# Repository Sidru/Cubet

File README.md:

# Cubet (CUBID-19) 

Cubet, a small single color led cube, build during the Covid-19 Quarantine

:warning: The README is still in working process

:warning: The Software works, but it must be improved. Trying to get the DMA to work with the Timer Counter to automatic set the LATCH output. The animations must be still coded (I've copied some animations and functions from [fuchsales/LED-Cube](https://github.com/fuchsalex/LED-Cube)

I always wanted a LED Cube, a compact one with smd leds. I also wanted to give KiCad a try (I've been Eagle user for a couple of years). That's why I started this mini project.

My goal was: 
- Small LED Cube, not bigger than 5cm
- No extra power needed (USB powered)
- Cheap (i.e. Shift Register instead of "expensive" LED Drivers, no SK6812/ws2811 leds)
- Designed with KiCad

I started with the Schematic and Layout in January, and the PCB came together with COVID, so I had plenty of time to solder.
I gave my cube the name of Cubet (catalan word for small cube), but CUBID is also a good name :)

The microcontroller is a SAMD21, with native USB, so no FTDI or similar is needed. It' a simple Arduino Zero compatible board, like the Feather M0 from Adafruit
It uses 74HC595 Shift Registers and a couple of transistors.

My tools are not the best one, and I realized I may need to buy better and new tools. For example my soldering iron is a cheap one and the soldering was quite a challenge (The head was too big for some components, and it didn't get hot enough). 
I also may need a Microscope, it's more pleasant than a magnifying glass. The tweezers were of course also too big. 

For the LED Matrix/Cube I need to develope a helping tool or something similar. My idea was to use 8 big holes in the PCB to put there 8 LEDS and solder them together to get a column. This didn't work as expected so I neede to solder without help.
I used 0.3mm Wire for the columns, and 0.2mm Wire for the rest.

## Getting Started

* Install KiCad and make changes to the schematic/layout (if needed)
* Get the PCB from your favourite Producer
* Solder all the components
* Flash the Bootloader (if needed)
* Flash the Software

#### Prerequisites

* A lot of time 
* Patience
* More patience
* Soldering skill
* JTAG Programmer (I used an J\-LINK EDU Mini)
* More time
* Did I mention patience?

### Installing 
#### Flashing the Bootloader
#### Flashing the Software

## Built With

* [KiCad](http://www.kicad-pcb.org)
* [PlatformIO](http://platformio.org)

## Authors

## License

This project is licensed under the Apache License - see the [LICENSE.md](LICENSE.md) file for tedtails

## Acknowledgments

[LED-Cube](https://github.com/fuchsalex/LED-Cube)
[Mini KiCad Tutorial](https://github.com/MalphasWats/hawk)
[KiCad Freerouting](https://github.com/miho/freerouting)
[Gerber Export](https://jnduli.co.ke/prepare-kicad-pcb-elecrow.html)
[PCB from Elecrow](https://www.elecrow.com/pcb-manufacturing.html)
[SAMD21](http://ww1.microchip.com/downloads/en/DeviceDoc/SAM_D21_DA1_Family_DataSheet_DS40001882F.pdf)
[SAMD21 GDB](https://learn.adafruit.com/debugging-the-samd21-with-gdb/setup)
[SAMD21 Bootloader Protection](https://roamingthings.de/posts/use-j-link-to-change-the-boot-loader-protection-of-a-sam-d21)
[Programming a SAMD bootloader using JLink & Linux](https://hackaday.io/page/5997-programming-a-samd-bootloader-using-jlink-linux)
[SAMD21\_DMA](https://aykevl.nl/2019/09/samd21-dma)
[Adafruit\_ZeroDMA](https://github.com/adafruit/Adafruit\_ZeroDMA)

## Future changes

* RGB leds 
* ESP32 for Blueetoth and WLAN
* SPI, I2C and UART connectors for hardware "upgrades"
* Battery connector and battery charging
* Maybe a 12x12x12 and a 16x16x16 version
* SD card for animations without programming

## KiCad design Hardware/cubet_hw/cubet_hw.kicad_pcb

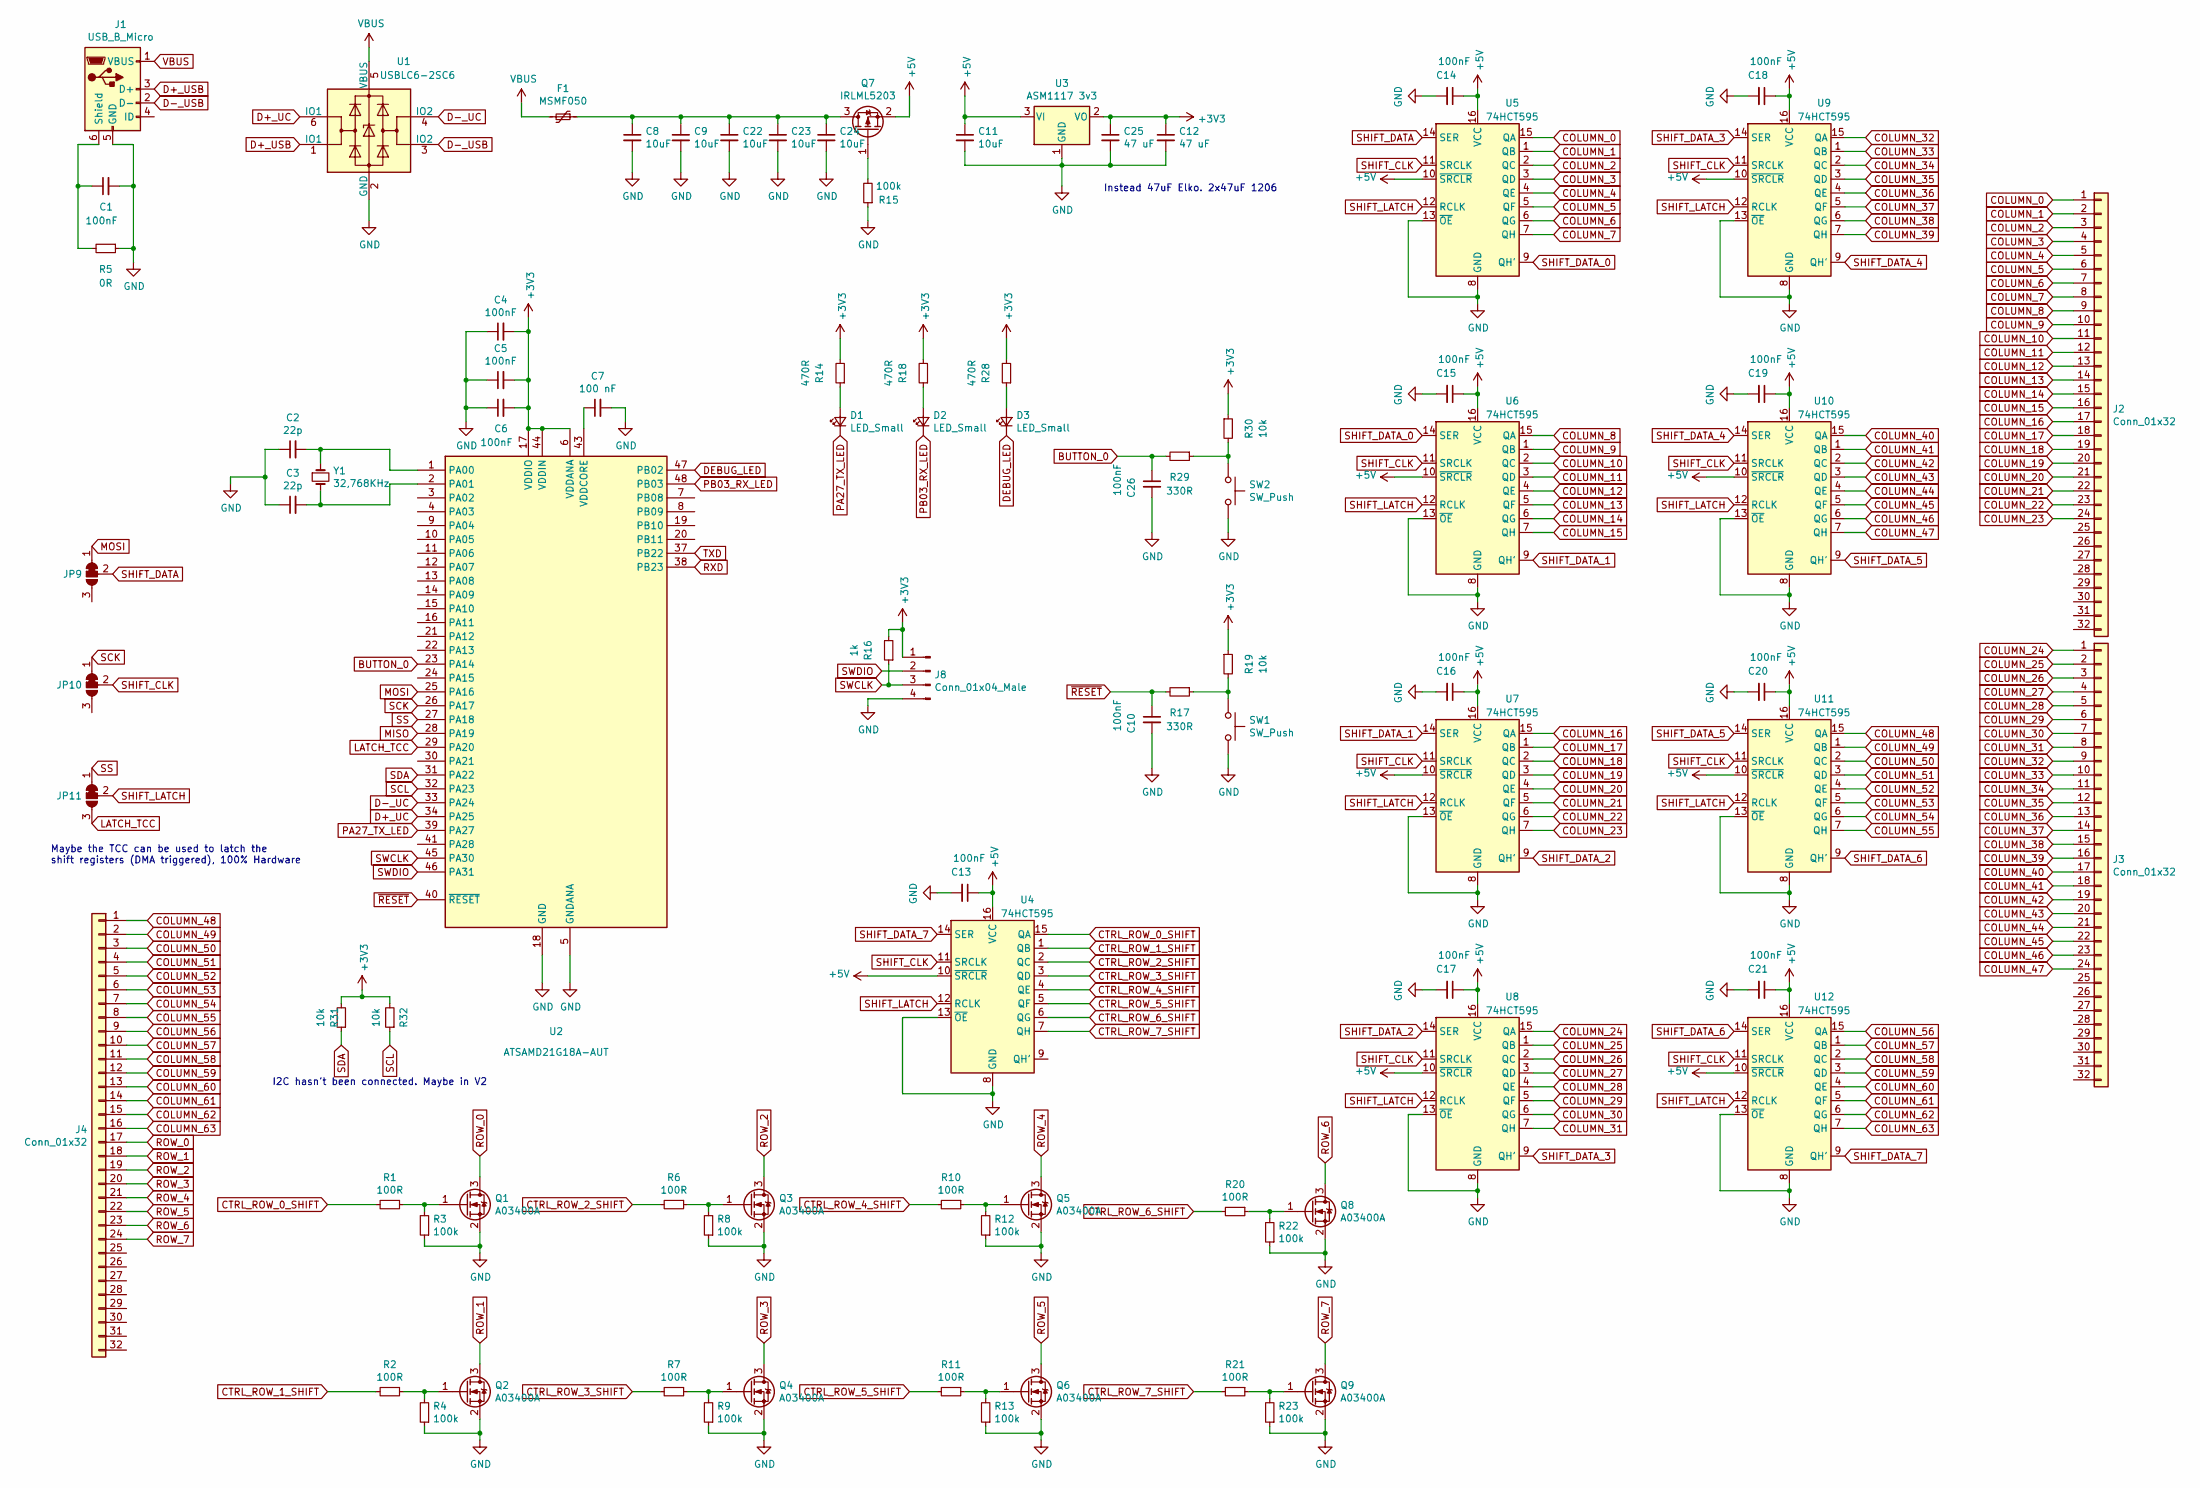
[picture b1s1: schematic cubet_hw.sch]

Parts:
C1, C4, C5, C6, C10, C13, C14, C15, C16, C17, C18, C19, C20, C21, C26: 100nF; C_0603_1608Metric
C2, C3: 22p; C_0603_1608Metric
C7: 100 nF; C_0603_1608Metric
C8, C9, C11, C22, C23, C24: 10uF; C_1206_3216Metric_Pad1.42x1.75mm_HandSolder
C12, C25: 47 uF; C_1206_3216Metric_Pad1.42x1.75mm_HandSolder
D1, D2, D3: LED_Small; LED_0603_1608Metric_Pad1.05x0.95mm_HandSolder
F1: MSMF050; Fuse_1812_4532Metric_Pad1.30x3.40mm_HandSolder
J1: USB_B_Micro; USB_Micro-B_Amphenol_10103594-0001LF_Horizontal
J2, J3, J4: Conn_01x32; PinSocket_1x32_P1.27mm_Vertical
J8: Conn_01x04_Male; PinHeader_1x04_P1.27mm_Horizontal
JP9, JP10, JP11: SolderJumper_3_Bridged12; SolderJumper-3_P1.3mm_Bridged12_RoundedPad1.0x1.5mm
Q1, Q2, Q3, Q4, Q5, Q6, Q8, Q9: A03400A; SOT-23
Q7: IRLML5203; SOT-23_Handsoldering
R1, R2, R6, R7, R10, R11, R20, R21: 100R; R_0603_1608Metric_Pad1.05x0.95mm_HandSolder
R3, R4, R8, R9, R12, R13, R22, R23: 100k; R_0603_1608Metric_Pad1.05x0.95mm_HandSolder
R5: 0R; R_0603_1608Metric
R14, R18, R28: 470R; R_0603_1608Metric_Pad1.05x0.95mm_HandSolder
R15: 100k; R_0603_1608Metric
R16: 1k; R_0603_1608Metric
R17, R29: 330R; R_0603_1608Metric
R19, R30: 10k; R_0603_1608Metric
R31, R32: 10k; R_0603_1608Metric_Pad1.05x0.95mm_HandSolder
SW1, SW2: SW_Push; SW_SPST_EVQP7A
U1: USBLC6-2SC6; SOT-23-6
U2: ATSAMD21G18A-AUT; TQFP-48_7x7mm_P0.5mm
U3: ASM1117 3v3; SOT-223
U4, U5, U6, U7, U8, U9, U10, U11, U12: 74HCT595; SOP-16_4.55x10.3mm_P1.27mm
Y1: 32,768KHz; Crystal_SMD_2012-2Pin_2.0x1.2mm_HandSoldering

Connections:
+3V3: C4.2, C5.2, C6.2, C12.1, C25.1, J8.1, R14.2, R16.2, R18.2, R19.1, R28.2, R30.1, R31.2, R32.2, U2.6 (VDDANA), U2.17 (VDDIO), U2.36 (VDDIO), U2.44 (VDDIN), U3.2 (VO)
+5V: C11.1, C13.1, C14.1, C15.1, C16.1, C17.1, C18.1, C19.1, C20.1, C21.1, Q7.2 (S), U3.3 (VI), U4.10 (~SRCLR), U4.16 (VCC), U5.10 (~SRCLR), U5.16 (VCC), U6.10 (~SRCLR), U6.16 (VCC), U7.10 (~SRCLR), U7.16 (VCC), U8.10 (~SRCLR), U8.16 (VCC), U9.10 (~SRCLR), U9.16 (VCC), U10.10 (~SRCLR), U10.16 (VCC), U11.10 (~SRCLR), U11.16 (VCC), U12.10 (~SRCLR), U12.16 (VCC)
BUTTON_0: C26.1, R29.2, U2.23 (PA14)
COLUMN_0: J2.1, U5.15 (QA)
COLUMN_1: J2.2, U5.1 (QB)
COLUMN_2: J2.3, U5.2 (QC)
COLUMN_3: J2.4, U5.3 (QD)
COLUMN_4: J2.5, U5.4 (QE)
COLUMN_5: J2.6, U5.5 (QF)
COLUMN_6: J2.7, U5.6 (QG)
COLUMN_7: J2.8, U5.7 (QH)
COLUMN_8: J2.9, U6.15 (QA)
COLUMN_9: J2.10, U6.1 (QB)
COLUMN_10: J2.11, U6.2 (QC)
COLUMN_11: J2.12, U6.3 (QD)
COLUMN_12: J2.13, U6.4 (QE)
COLUMN_13: J2.14, U6.5 (QF)
COLUMN_14: J2.15, U6.6 (QG)
COLUMN_15: J2.16, U6.7 (QH)
COLUMN_16: J2.17, U7.15 (QA)
COLUMN_17: J2.18, U7.1 (QB)
COLUMN_18: J2.19, U7.2 (QC)
COLUMN_19: J2.20, U7.3 (QD)
COLUMN_20: J2.21, U7.4 (QE)
COLUMN_21: J2.22, U7.5 (QF)
COLUMN_22: J2.23, U7.6 (QG)
COLUMN_23: J2.24, U7.7 (QH)
COLUMN_24: J3.1, U8.15 (QA)
COLUMN_25: J3.2, U8.1 (QB)
COLUMN_26: J3.3, U8.2 (QC)
COLUMN_27: J3.4, U8.3 (QD)
COLUMN_28: J3.5, U8.4 (QE)
COLUMN_29: J3.6, U8.5 (QF)
COLUMN_30: J3.7, U8.6 (QG)
COLUMN_31: J3.8, U8.7 (QH)
COLUMN_32: J3.9, U9.15 (QA)
COLUMN_33: J3.10, U9.1 (QB)
COLUMN_34: J3.11, U9.2 (QC)
COLUMN_35: J3.12, U9.3 (QD)
COLUMN_36: J3.13, U9.4 (QE)
COLUMN_37: J3.14, U9.5 (QF)
COLUMN_38: J3.15, U9.6 (QG)
COLUMN_39: J3.16, U9.7 (QH)
COLUMN_40: J3.17, U10.15 (QA)
COLUMN_41: J3.18, U10.1 (QB)
COLUMN_42: J3.19, U10.2 (QC)
COLUMN_43: J3.20, U10.3 (QD)
COLUMN_44: J3.21, U10.4 (QE)
COLUMN_45: J3.22, U10.5 (QF)
COLUMN_46: J3.23, U10.6 (QG)
COLUMN_47: J3.24, U10.7 (QH)
COLUMN_48: J4.1, U11.15 (QA)
COLUMN_49: J4.2, U11.1 (QB)
COLUMN_50: J4.3, U11.2 (QC)
COLUMN_51: J4.4, U11.3 (QD)
COLUMN_52: J4.5, U11.4 (QE)
COLUMN_53: J4.6, U11.5 (QF)
COLUMN_54: J4.7, U11.6 (QG)
COLUMN_55: J4.8, U11.7 (QH)
COLUMN_56: J4.9, U12.15 (QA)
COLUMN_57: J4.10, U12.1 (QB)
COLUMN_58: J4.11, U12.2 (QC)
COLUMN_59: J4.12, U12.3 (QD)
COLUMN_60: J4.13, U12.4 (QE)
COLUMN_61: J4.14, U12.5 (QF)
COLUMN_62: J4.15, U12.6 (QG)
COLUMN_63: J4.16, U12.7 (QH)
CTRL_ROW_0_SHIFT: R1.2, U4.15 (QA)
CTRL_ROW_0_UC: U2.9 (PA04)
CTRL_ROW_1_SHIFT: R2.2, U4.1 (QB)
CTRL_ROW_1_UC: U2.10 (PA05)
CTRL_ROW_2_SHIFT: R6.2, U4.2 (QC)
CTRL_ROW_2_UC: U2.11 (PA06)
CTRL_ROW_3_SHIFT: R7.2, U4.3 (QD)
CTRL_ROW_3_UC: U2.12 (PA07)
CTRL_ROW_4_SHIFT: R10.2, U4.4 (QE)
CTRL_ROW_4_UC: U2.13 (PA08)
CTRL_ROW_5_SHIFT: R11.2, U4.5 (QF)
CTRL_ROW_5_UC: U2.14 (PA09)
CTRL_ROW_6_SHIFT: R20.2, U4.6 (QG)
CTRL_ROW_6_UC: U2.15 (PA10)
CTRL_ROW_7_SHIFT: R21.2, U4.7 (QH)
CTRL_ROW_7_UC: U2.16 (PA11)
D+_UC: U1.6 (IO1), U2.34 (PA25)
D+_USB: J1.3 (D+), U1.1 (IO1)
D-_UC: U1.4 (IO2), U2.33 (PA24)
D-_USB: J1.2 (D-), U1.3 (IO2)
DEBUG_LED: D3.1 (K), U2.47 (PB02)
GND: C1.2, C2.1, C3.1, C4.1, C5.1, C6.1, C7.2, C8.2, C9.2, C10.2, C11.2, C12.2, C13.2, C14.2, C15.2, C16.2, C17.2, C18.2, C19.2, C20.2, C21.2, C22.2, C23.2, C24.2, C25.2, C26.2, J1.5 (GND), J8.4, Q1.2 (S), Q2.2 (S), Q3.2 (S), Q4.2 (S), Q5.2 (S), Q6.2 (S), Q8.2 (S), Q9.2 (S), R3.1, R4.1, R5.1, R8.1, R9.1, R12.1, R13.1, R15.1, R22.1, R23.1, SW1.2, SW2.2, U1.2 (GND), U2.5 (GNDANA), U2.18 (GND), U2.35 (GND), U2.42 (GND), U3.1 (GND), U4.8 (GND), U4.13 (~OE), U5.8 (GND), U5.13 (~OE), U6.8 (GND), U6.13 (~OE), U7.8 (GND), U7.13 (~OE), U8.8 (GND), U8.13 (~OE), U9.8 (GND), U9.13 (~OE), U10.8 (GND), U10.13 (~OE), U11.8 (GND), U11.13 (~OE), U12.8 (GND), U12.13 (~OE)
LATCH_TCC: JP11.3 (B), U2.29 (PA20)
MISO: U2.28 (PA19)
MOSI: JP9.1 (A), U2.25 (PA16)
unnamed: C1.1, J1.6 (Shield), R5.2
unnamed: C2.2, U2.1 (PA00), Y1.1
unnamed: C3.2, U2.2 (PA01), Y1.2
unnamed: C7.1, U2.43 (VDDCORE)
unnamed: C8.1, C9.1, C22.1, C23.1, C24.1, F1.1, Q7.3 (D)
unnamed: D1.2 (A), R14.1
unnamed: D2.2 (A), R18.1
unnamed: D3.2 (A), R28.1
unnamed: Q1.1 (G), R1.1, R3.2
unnamed: Q2.1 (G), R2.1, R4.2
unnamed: Q3.1 (G), R6.1, R8.2
unnamed: Q4.1 (G), R7.1, R9.2
unnamed: Q5.1 (G), R10.1, R12.2
unnamed: Q6.1 (G), R11.1, R13.2
unnamed: Q7.1 (G), R15.2
unnamed: Q8.1 (G), R20.1, R22.2
unnamed: Q9.1 (G), R21.1, R23.2
unnamed: R17.1, R19.2, SW1.1
unnamed: R29.1, R30.2, SW2.1
PA27_TX_LED: D1.1 (K), U2.39 (PA27)
PB03_RX_LED: D2.1 (K), U2.48 (PB03)
PB10_S4_SPI_MOSI: U2.19 (PB10)
PB11_S4_SPI_SCK: U2.20 (PB11)
PB12_S4_SPI_MISO: U2.21 (PA12)
ROW_0: J4.17, Q1.3 (D)
ROW_1: J4.18, Q2.3 (D)
ROW_2: J4.19, Q3.3 (D)
ROW_3: J4.20, Q4.3 (D)
ROW_4: J4.21, Q5.3 (D)
ROW_5: J4.22, Q6.3 (D)
ROW_6: J4.23, Q8.3 (D)
ROW_7: J4.24, Q9.3 (D)
RXD: U2.38 (PB23)
SCK: JP10.1 (A), U2.26 (PA17)
SCL: R32.1, U2.32 (PA23)
SDA: R31.1, U2.31 (PA22)
SHIFT_CLK: JP10.2 (C), U4.11 (SRCLK), U5.11 (SRCLK), U6.11 (SRCLK), U7.11 (SRCLK), U8.11 (SRCLK), U9.11 (SRCLK), U10.11 (SRCLK), U11.11 (SRCLK), U12.11 (SRCLK)
SHIFT_DATA: JP9.2 (C), U5.14 (SER)
SHIFT_DATA_0: U5.9 (QH'), U6.14 (SER)
SHIFT_DATA_1: U6.9 (QH'), U7.14 (SER)
SHIFT_DATA_2: U7.9 (QH'), U8.14 (SER)
SHIFT_DATA_3: U8.9 (QH'), U9.14 (SER)
SHIFT_DATA_4: U9.9 (QH'), U10.14 (SER)
SHIFT_DATA_5: U10.9 (QH'), U11.14 (SER)
SHIFT_DATA_6: U11.9 (QH'), U12.14 (SER)
SHIFT_DATA_7: U4.14 (SER), U12.9 (QH')
SHIFT_LATCH: JP11.2 (C), U4.12 (RCLK), U5.12 (RCLK), U6.12 (RCLK), U7.12 (RCLK), U8.12 (RCLK), U9.12 (RCLK), U10.12 (RCLK), U11.12 (RCLK), U12.12 (RCLK)
SS: JP11.1 (A), U2.27 (PA18)
SWCLK: J8.3, R16.1, U2.45 (PA30)
SWDIO: J8.2, U2.46 (PA31)
TXD: U2.37 (PB22)
VBUS: F1.2, J1.1 (VBUS), U1.5 (VBUS)
~RESET~: C10.1, R17.2, U2.40 (~RESET)

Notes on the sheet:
Instead 47uF Elko. 2x47uF 1206
Maybe the TCC can be used to latch the shift registers (DMA triggered), 100% Hardware
I2C hasn't been connected. Maybe in V2

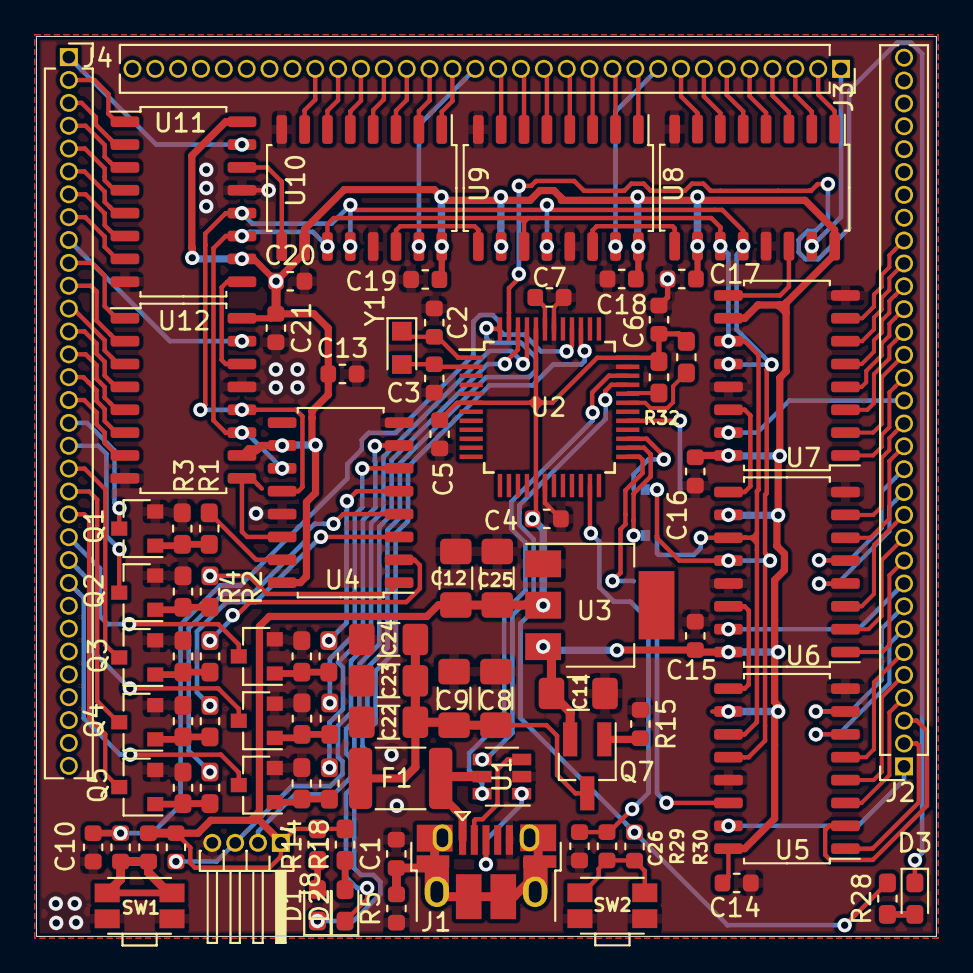
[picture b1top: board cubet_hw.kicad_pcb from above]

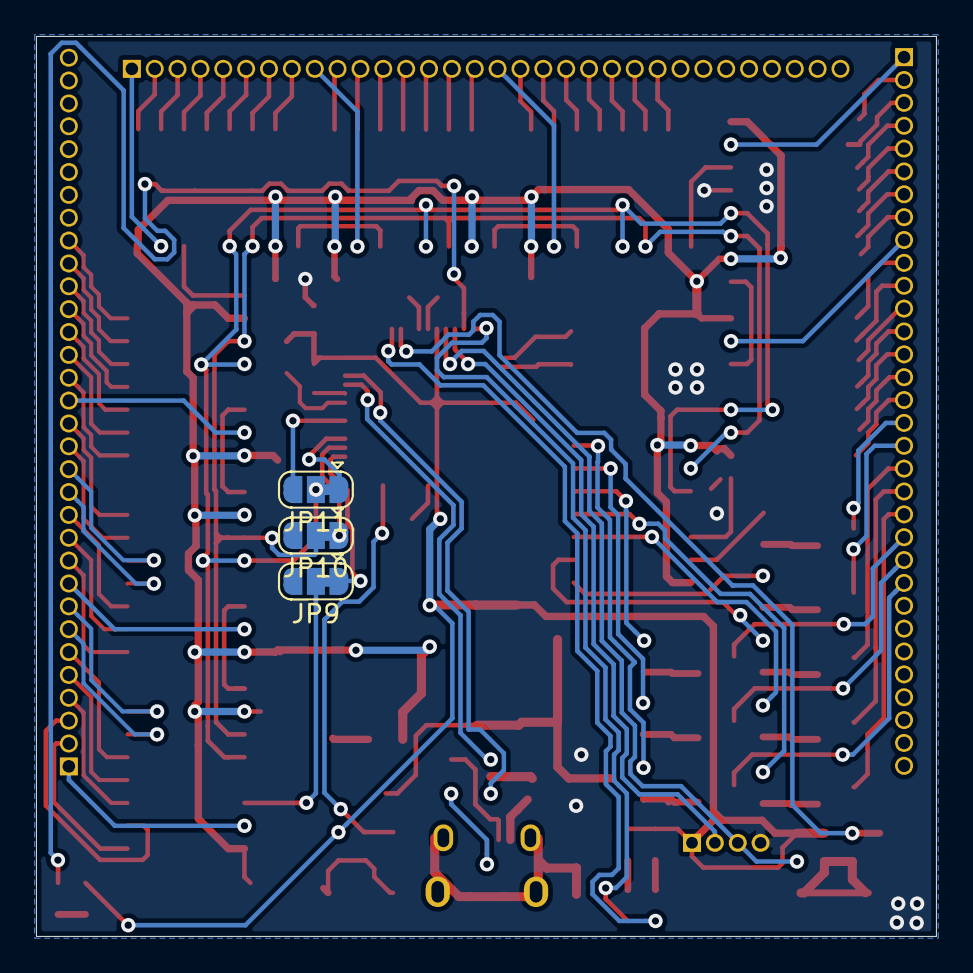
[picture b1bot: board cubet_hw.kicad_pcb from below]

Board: 2 copper layers, 50.0 x 50.0 mm, 90 parts (3 on the bottom side), 131 nets.

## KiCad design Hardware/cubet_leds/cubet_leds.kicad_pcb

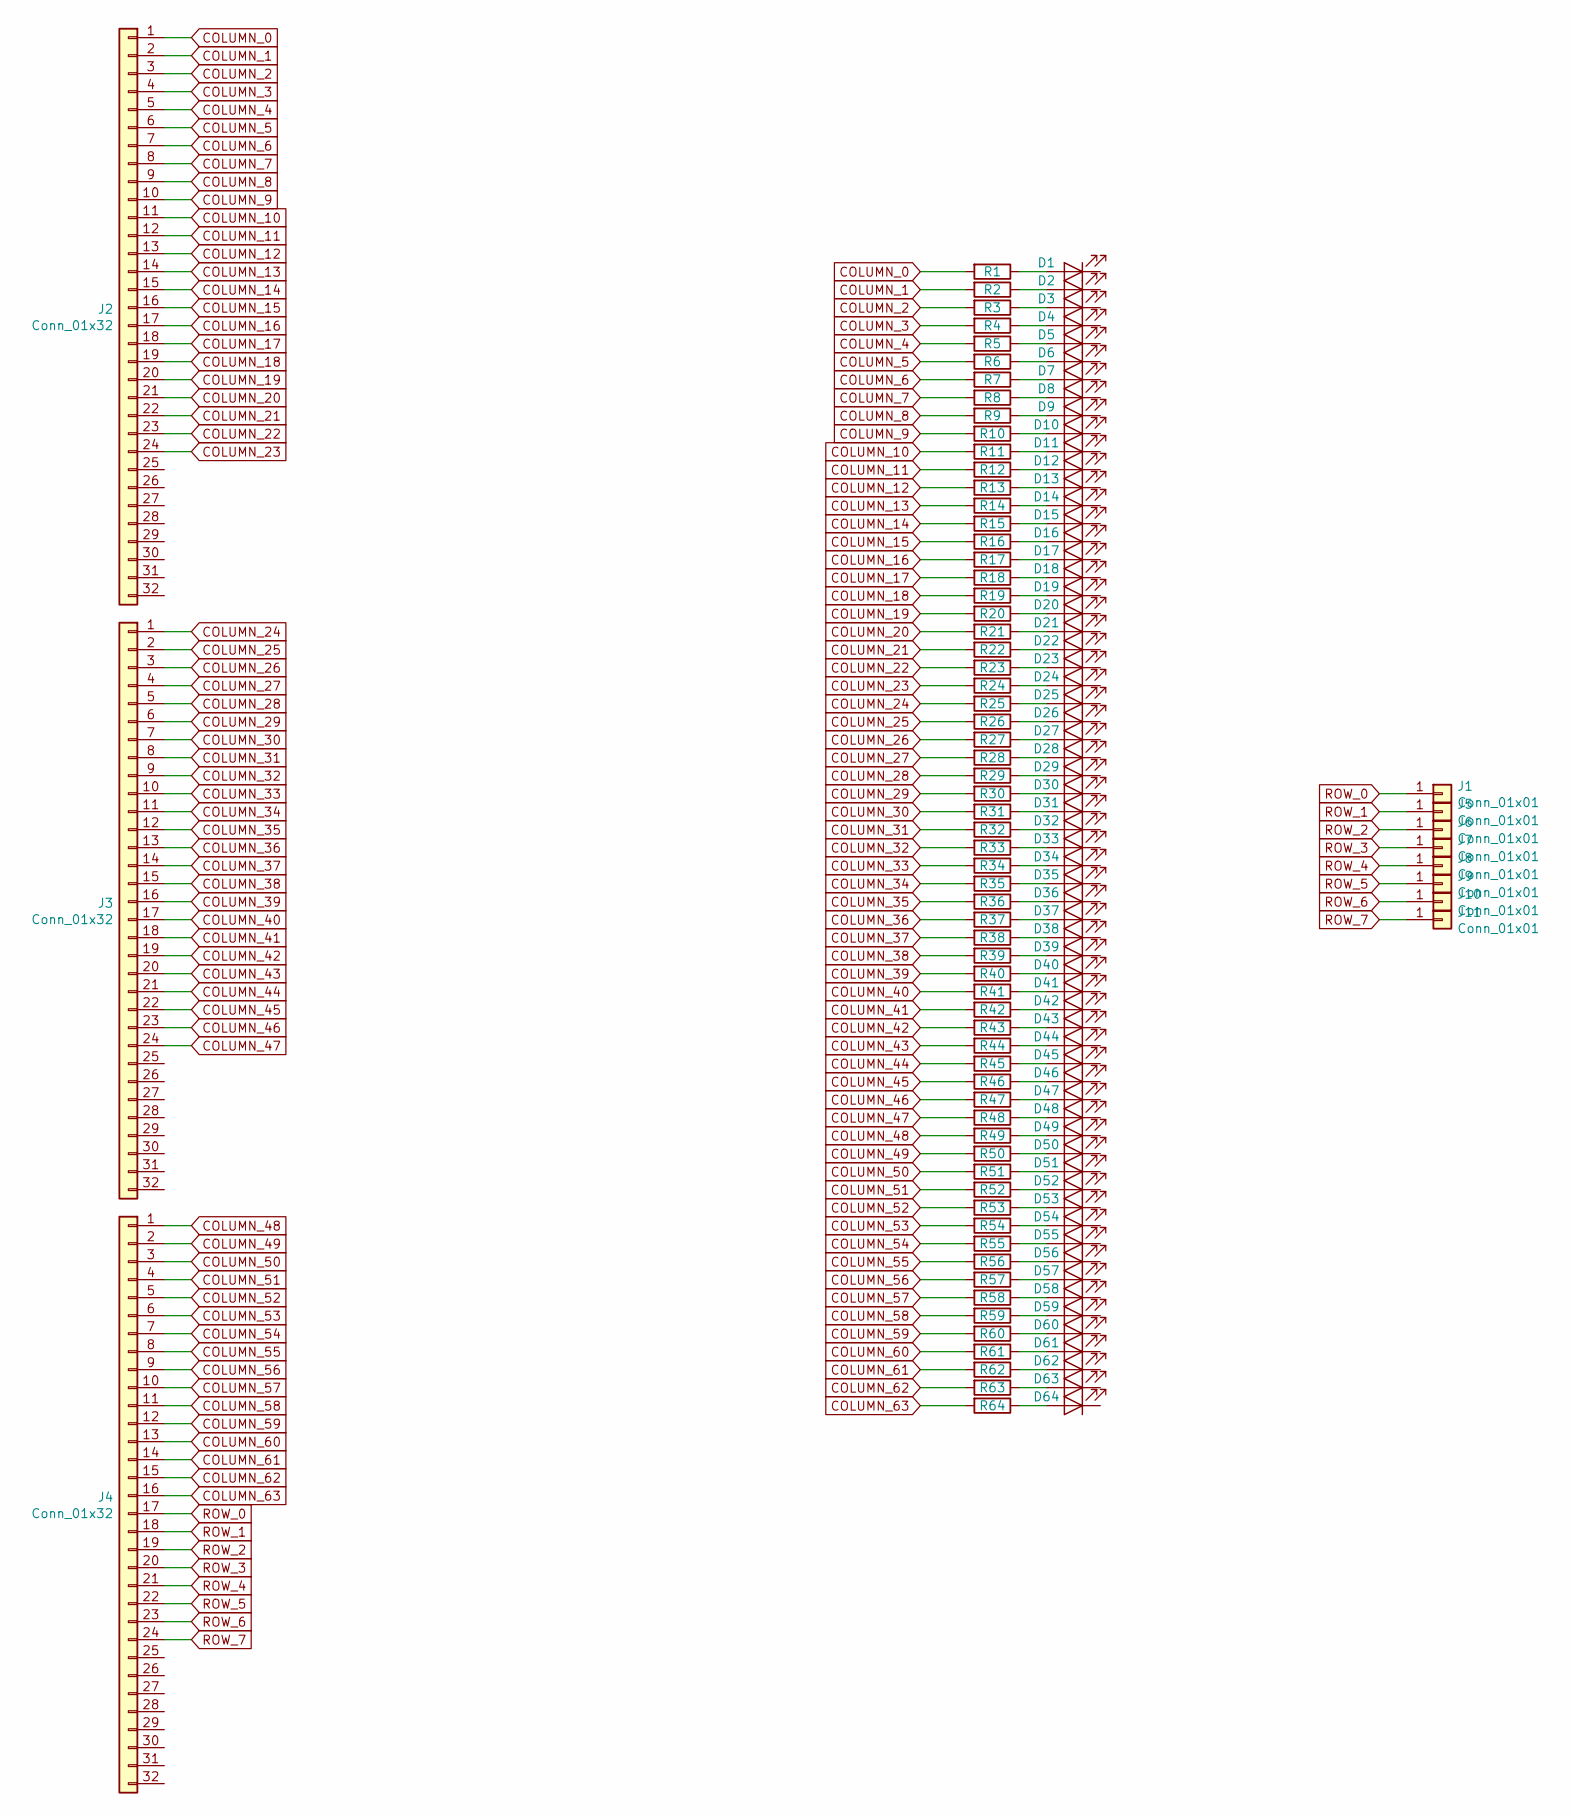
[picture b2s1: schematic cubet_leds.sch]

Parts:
D1, D2, D3, D4, D5, D6, D7, D8, D9, D10, D11, D12, D13, D14, D15, D16, D17, D18, D19, D20, D21, D22, D23, D24, D25, D26, D27, D28, D29, D30, D31, D32, D33, D34, D35, D36, D37, D38, D39, D40, D41, D42, D43, D44, D45, D46, D47, D48, D49, D50, D51, D52, D53, D54, D55, D56, D57, D58, D59, D60, D61, D62, D63, D64: LED; LED_0603_03Drill
J1, J5, J6, J7, J8, J9, J10, J11: Conn_01x01; TestPoint_THTPad_D1.0mm_Drill0.3mm
J2, J3, J4: Conn_01x32; PinSocket_1x32_P1.27mm_Vertical
R1, R2, R3, R4, R5, R6, R7, R8, R9, R10, R11, R12, R13, R14, R15, R16, R17, R18, R19, R20, R21, R22, R23, R24, R25, R26, R27, R28, R29, R30, R31, R32, R33, R34, R35, R36, R37, R38, R39, R40, R41, R42, R43, R44, R45, R46, R47, R48, R49, R50, R51, R52, R53, R54, R55, R56, R57, R58, R59, R60, R61, R62, R63, R64: R; R_0603_1608Metric

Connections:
COLUMN_0: J2.1, R1.2
COLUMN_1: J2.2, R2.2
COLUMN_2: J2.3, R3.2
COLUMN_3: J2.4, R4.2
COLUMN_4: J2.5, R5.2
COLUMN_5: J2.6, R6.2
COLUMN_6: J2.7, R7.2
COLUMN_7: J2.8, R8.2
COLUMN_8: J2.9, R9.2
COLUMN_9: J2.10, R10.2
COLUMN_10: J2.11, R11.2
COLUMN_11: J2.12, R12.2
COLUMN_12: J2.13, R13.2
COLUMN_13: J2.14, R14.2
COLUMN_14: J2.15, R15.2
COLUMN_15: J2.16, R16.2
COLUMN_16: J2.17, R17.2
COLUMN_17: J2.18, R18.2
COLUMN_18: J2.19, R19.2
COLUMN_19: J2.20, R20.2
COLUMN_20: J2.21, R21.2
COLUMN_21: J2.22, R22.2
COLUMN_22: J2.23, R23.2
COLUMN_23: J2.24, R24.2
COLUMN_24: J3.1, R25.2
COLUMN_25: J3.2, R26.2
COLUMN_26: J3.3, R27.2
COLUMN_27: J3.4, R28.2
COLUMN_28: J3.5, R29.2
COLUMN_29: J3.6, R30.2
COLUMN_30: J3.7, R31.2
COLUMN_31: J3.8, R32.2
COLUMN_32: J3.9, R33.2
COLUMN_33: J3.10, R34.2
COLUMN_34: J3.11, R35.2
COLUMN_35: J3.12, R36.2
COLUMN_36: J3.13, R37.2
COLUMN_37: J3.14, R38.2
COLUMN_38: J3.15, R39.2
COLUMN_39: J3.16, R40.2
COLUMN_40: J3.17, R41.2
COLUMN_41: J3.18, R42.2
COLUMN_42: J3.19, R43.2
COLUMN_43: J3.20, R44.2
COLUMN_44: J3.21, R45.2
COLUMN_45: J3.22, R46.2
COLUMN_46: J3.23, R47.2
COLUMN_47: J3.24, R48.2
COLUMN_48: J4.1, R49.2
COLUMN_49: J4.2, R50.2
COLUMN_50: J4.3, R51.2
COLUMN_51: J4.4, R52.2
COLUMN_52: J4.5, R53.2
COLUMN_53: J4.6, R54.2
COLUMN_54: J4.7, R55.2
COLUMN_55: J4.8, R56.2
COLUMN_56: J4.9, R57.2
COLUMN_57: J4.10, R58.2
COLUMN_58: J4.11, R59.2
COLUMN_59: J4.12, R60.2
COLUMN_60: J4.13, R61.2
COLUMN_61: J4.14, R62.2
COLUMN_62: J4.15, R63.2
COLUMN_63: J4.16, R64.2
unnamed: D1.2 (A), R1.1
unnamed: D2.2 (A), R2.1
unnamed: D3.2 (A), R3.1
unnamed: D4.2 (A), R4.1
unnamed: D5.2 (A), R5.1
unnamed: D6.2 (A), R6.1
unnamed: D7.2 (A), R7.1
unnamed: D8.2 (A), R8.1
unnamed: D9.2 (A), R9.1
unnamed: D10.2 (A), R10.1
unnamed: D11.2 (A), R11.1
unnamed: D12.2 (A), R12.1
unnamed: D13.2 (A), R13.1
unnamed: D14.2 (A), R14.1
unnamed: D15.2 (A), R15.1
unnamed: D16.2 (A), R16.1
unnamed: D17.2 (A), R17.1
unnamed: D18.2 (A), R18.1
unnamed: D19.2 (A), R19.1
unnamed: D20.2 (A), R20.1
unnamed: D21.2 (A), R21.1
unnamed: D22.2 (A), R22.1
unnamed: D23.2 (A), R23.1
unnamed: D24.2 (A), R24.1
unnamed: D25.2 (A), R25.1
unnamed: D26.2 (A), R26.1
unnamed: D27.2 (A), R27.1
unnamed: D28.2 (A), R28.1
unnamed: D29.2 (A), R29.1
unnamed: D30.2 (A), R30.1
unnamed: D31.2 (A), R31.1
unnamed: D32.2 (A), R32.1
unnamed: D33.2 (A), R33.1
unnamed: D34.2 (A), R34.1
unnamed: D35.2 (A), R35.1
unnamed: D36.2 (A), R36.1
unnamed: D37.2 (A), R37.1
unnamed: D38.2 (A), R38.1
unnamed: D39.2 (A), R39.1
unnamed: D40.2 (A), R40.1
unnamed: D41.2 (A), R41.1
unnamed: D42.2 (A), R42.1
unnamed: D43.2 (A), R43.1
unnamed: D44.2 (A), R44.1
unnamed: D45.2 (A), R45.1
unnamed: D46.2 (A), R46.1
unnamed: D47.2 (A), R47.1
unnamed: D48.2 (A), R48.1
unnamed: D49.2 (A), R49.1
unnamed: D50.2 (A), R50.1
unnamed: D51.2 (A), R51.1
unnamed: D52.2 (A), R52.1
unnamed: D53.2 (A), R53.1
unnamed: D54.2 (A), R54.1
unnamed: D55.2 (A), R55.1
unnamed: D56.2 (A), R56.1
unnamed: D57.2 (A), R57.1
unnamed: D58.2 (A), R58.1
unnamed: D59.2 (A), R59.1
unnamed: D60.2 (A), R60.1
unnamed: D61.2 (A), R61.1
unnamed: D62.2 (A), R62.1
unnamed: D63.2 (A), R63.1
unnamed: D64.2 (A), R64.1
ROW_0: J1.1, J4.17
ROW_1: J4.18, J5.1
ROW_2: J4.19, J6.1
ROW_3: J4.20, J7.1
ROW_4: J4.21, J8.1
ROW_5: J4.22, J9.1
ROW_6: J4.23, J10.1
ROW_7: J4.24, J11.1

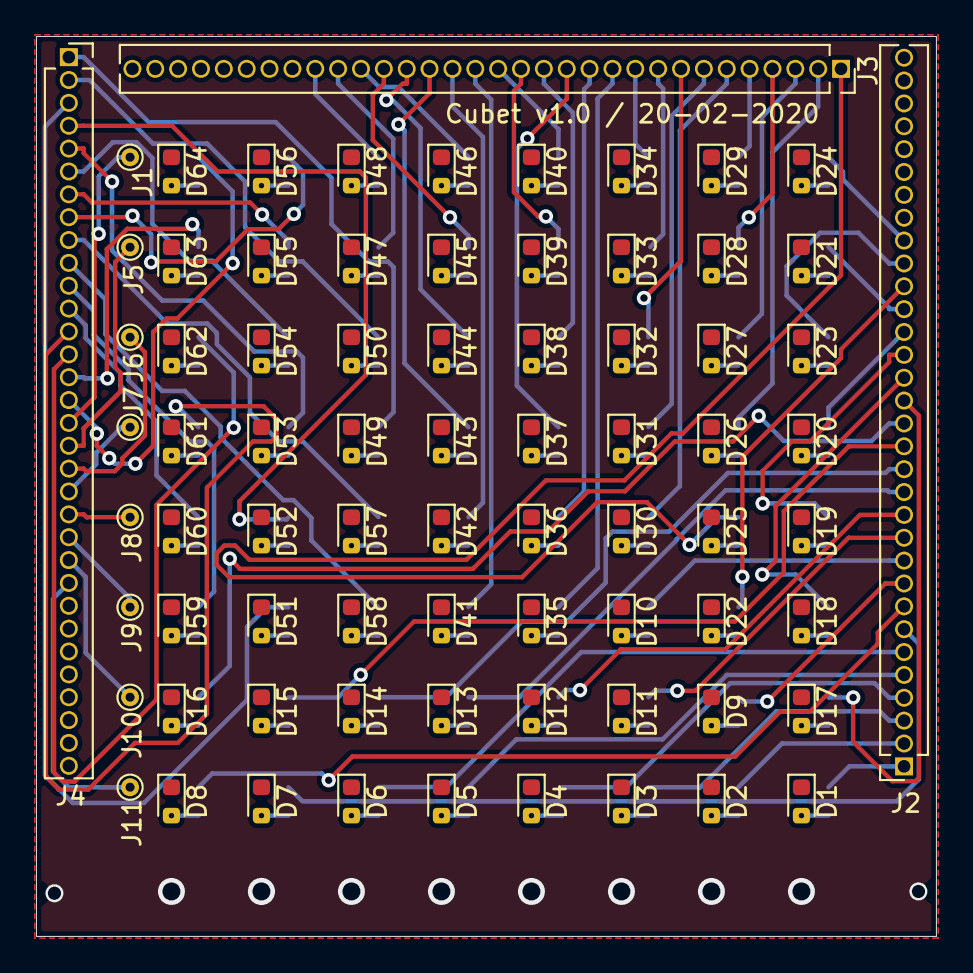
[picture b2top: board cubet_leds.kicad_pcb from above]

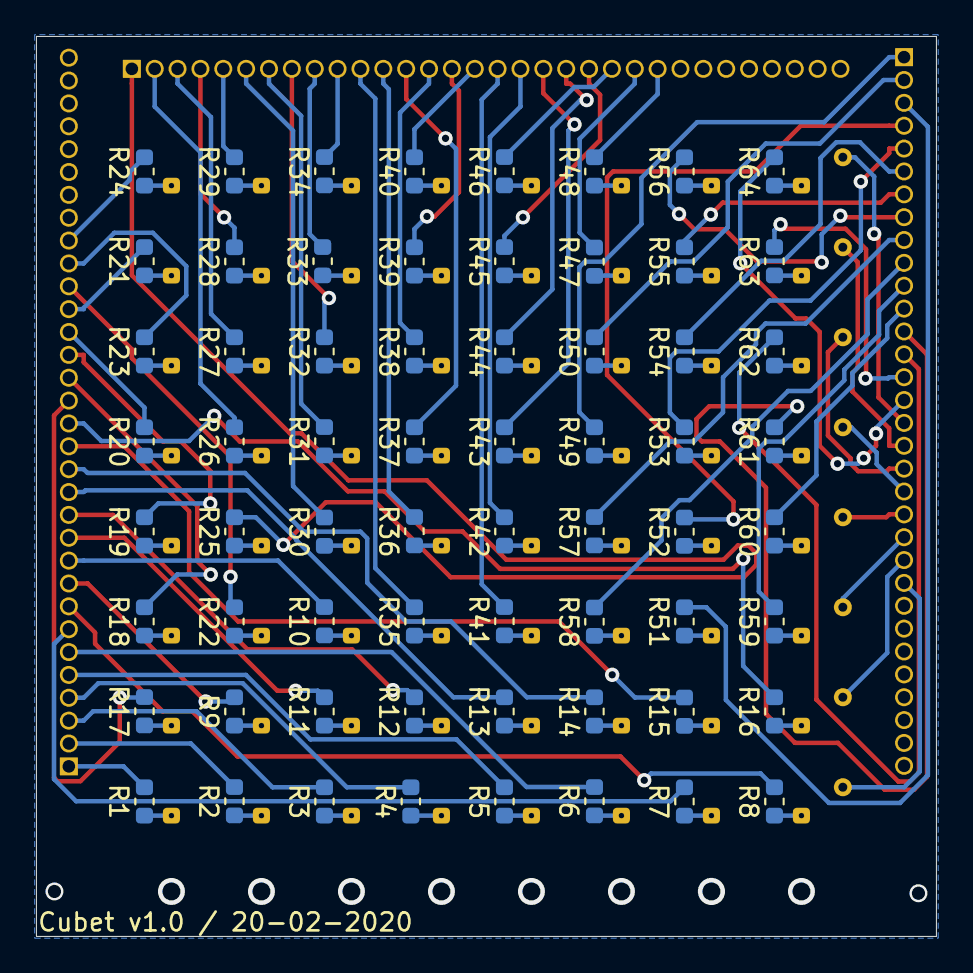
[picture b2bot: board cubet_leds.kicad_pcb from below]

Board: 2 copper layers, 50.0 x 50.0 mm, 139 parts (64 on the bottom side), 136 nets.

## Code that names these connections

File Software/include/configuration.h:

#ifndef CONFIGURATION_H
#define CONFIGURATION_H

/* PINS */
#define DEBUG_LED_PIN   19  // PIN_PB02 -> 19 for Arduino
#define BUTTON_PIN      2   // PIN_PA14 -> 2 for Arduino
#define SHIFT_DATA_PIN  11  // PIN_PA16 -> 11 for Arduino
#define SHIFT_CLK_PIN   13  // PIN_PA17 -> 13 for Arduino
#define SHIFT_LATCH_PIN 10  // PIN_PA18 -> 10 for Arduino
#define SHIFT_READ_PIN  9   // PIN_PA07 -> 9 for Arduino. Not used, only to test the Shifty library


/* CUBE */
#define SIZE_OF_X 8     // Number of leds in x 
#define SIZE_OF_Y 8     // Number of leds in y
#define SIZE_OF_Z 8     // Number of leds in z

#define SINGLE_COLOR_CUBE       // Uncomment this in case you are using a single LED Cube
//#define MULTIPLE_COLOR_CUBE   // Uncomennt this in case you are using an RGB LED Cube


#define FRAMES_PER_SECOND   25
#define PWM_RESOLUTION      32 
//#define PWM


#define CUBE_REFRESH_MS 1


/* SHIFT REGISTER */
//#define SHIFT_SOFTWARE
//#define SHIFT_SPI
#define SHIFT_SPI_DMA
//#define SHIFT_SPI_DMA_TC




#define ARRAY_LAYER_SIZE (((uint32_t)SIZE_OF_X * (uint32_t)SIZE_OF_Y)/8 + ((uint32_t)SIZE_OF_Z/8))

#endif

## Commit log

2019-10-06 Schaltplan fast fertig
2020-02-01 bootloader flashed, ready to program
2020-02-01 Unnötige Dateien löschen
2020-02-01 First hardware tests...
2020-02-21 LEDs PCB bestellt
2020-04-16 First working SPI. First work in README
2020-04-22 Importing effects from Alex Fuchs Cube
2020-04-25 some pictures added
2020-04-26 resisze gif
2020-04-26 gif resize to 320px
2020-05-06 First Text Animation
